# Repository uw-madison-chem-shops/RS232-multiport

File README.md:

# RS232 Multiport

## Repository

This is an open source hardware project licensed under the CERN Open Hardware Licence Version 2 - Permissive.
Please see the LICENSE file for the complete license.

## PCB

This PCB was designed using KiCAD version 7.
Refer to `mqtt_particle_sensor.pdf` for schematic.
PCB images generated with [tracespace](https://github.com/tracespace/tracespace) follow.

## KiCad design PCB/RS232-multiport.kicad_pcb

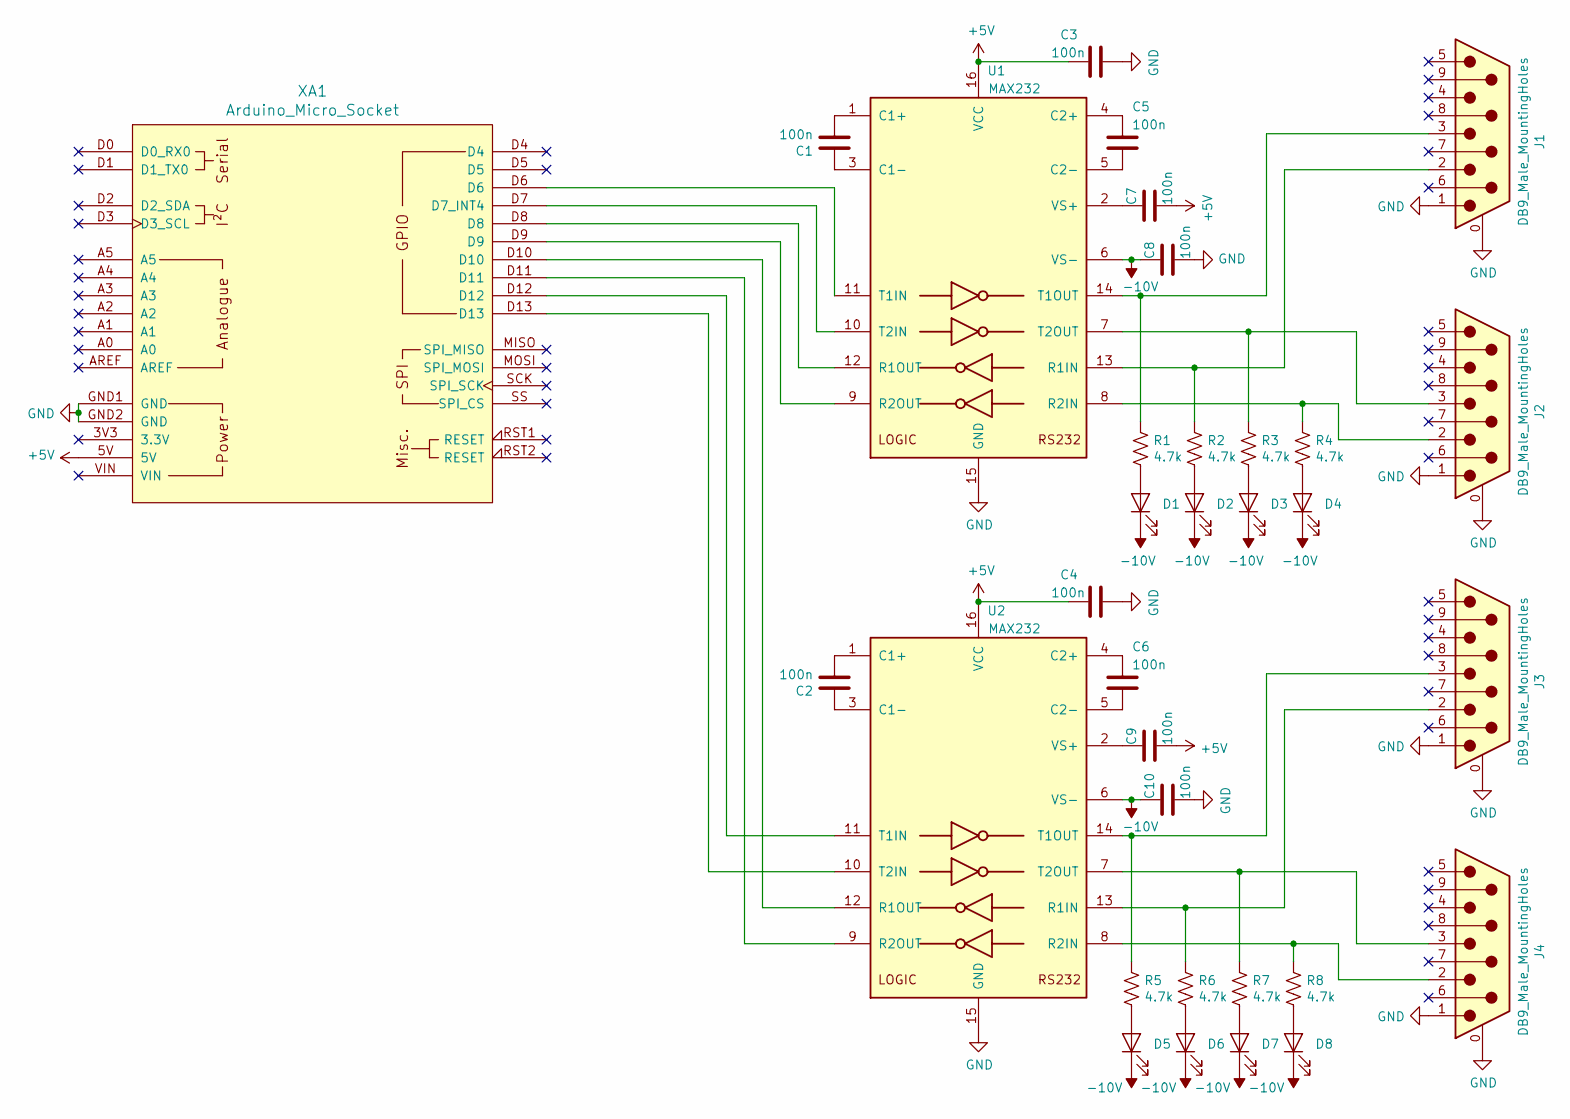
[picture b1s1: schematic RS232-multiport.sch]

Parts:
C1, C2, C3, C4, C5, C6, C7, C8, C9, C10: 100n; C_1206_3216Metric_Pad1.42x1.75mm_HandSolder
D1, D2, D3, D4, D5, D6, D7, D8: LED; LED_1206_3216Metric_Pad1.42x1.75mm_HandSolder
J1, J2, J3, J4: DB9_Male_MountingHoles; DSUB-9_Male_Horizontal_P2.77x2.84mm_EdgePinOffset9.90mm_Hou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
R1, R2, R3, R4, R5, R6, R7, R8: 4.7k; R_1206_3216Metric_Pad1.42x1.75mm_HandSolder
U1, U2: MAX232; DIP-16_W7.62mm_Socket_LongPads
XA1: Arduino_Micro_Socket

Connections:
+5V: C3.2, C4.2, C7.2, C9.2, U1.16 (VCC), U2.16 (VCC), XA1.5V
-10V: C8.1, C10.1, D1.1 (K), D2.1 (K), D3.1 (K), D4.1 (K), D5.1 (K), D6.1 (K), D7.1 (K), D8.1 (K), U1.6 (VS-), U2.6 (VS-)
GND: C3.1, C4.1, C8.2, C10.2, J1.0 (PAD), J1.1, J2.0 (PAD), J2.1, J3.0 (PAD), J3.1, J4.0 (PAD), J4.1, U1.15 (GND), U2.15 (GND), XA1.GND1 (GND), XA1.GND2 (GND)
unnamed: C1.1, U1.3 (C1-)
unnamed: C1.2, U1.1 (C1+)
unnamed: C2.1, U2.3 (C1-)
unnamed: C2.2, U2.1 (C1+)
unnamed: C5.1, U1.4 (C2+)
unnamed: C5.2, U1.5 (C2-)
unnamed: C6.1, U2.4 (C2+)
unnamed: C6.2, U2.5 (C2-)
unnamed: C7.1, U1.2 (VS+)
unnamed: C9.1, U2.2 (VS+)
unnamed: D1.2 (A), R1.2
unnamed: D2.2 (A), R2.2
unnamed: D3.2 (A), R3.2
unnamed: D4.2 (A), R4.2
unnamed: D5.2 (A), R5.2
unnamed: D6.2 (A), R6.2
unnamed: D7.2 (A), R7.2
unnamed: D8.2 (A), R8.2
unnamed: J1.2, R2.1, U1.13 (R1IN)
unnamed: J1.3, R1.1, U1.14 (T1OUT)
unnamed: J2.2, R4.1, U1.8 (R2IN)
unnamed: J2.3, R3.1, U1.7 (T2OUT)
unnamed: J3.2, R6.1, U2.13 (R1IN)
unnamed: J3.3, R5.1, U2.14 (T1OUT)
unnamed: J4.2, R8.1, U2.8 (R2IN)
unnamed: J4.3, R7.1, U2.7 (T2OUT)
unnamed: U1.9 (R2OUT), XA1.D9
unnamed: U1.10 (T2IN), XA1.D7 (D7_INT4)
unnamed: U1.11 (T1IN), XA1.D6
unnamed: U1.12 (R1OUT), XA1.D8
unnamed: U2.9 (R2OUT), XA1.D11
unnamed: U2.10 (T2IN), XA1.D13
unnamed: U2.11 (T1IN), XA1.D12
unnamed: U2.12 (R1OUT), XA1.D10

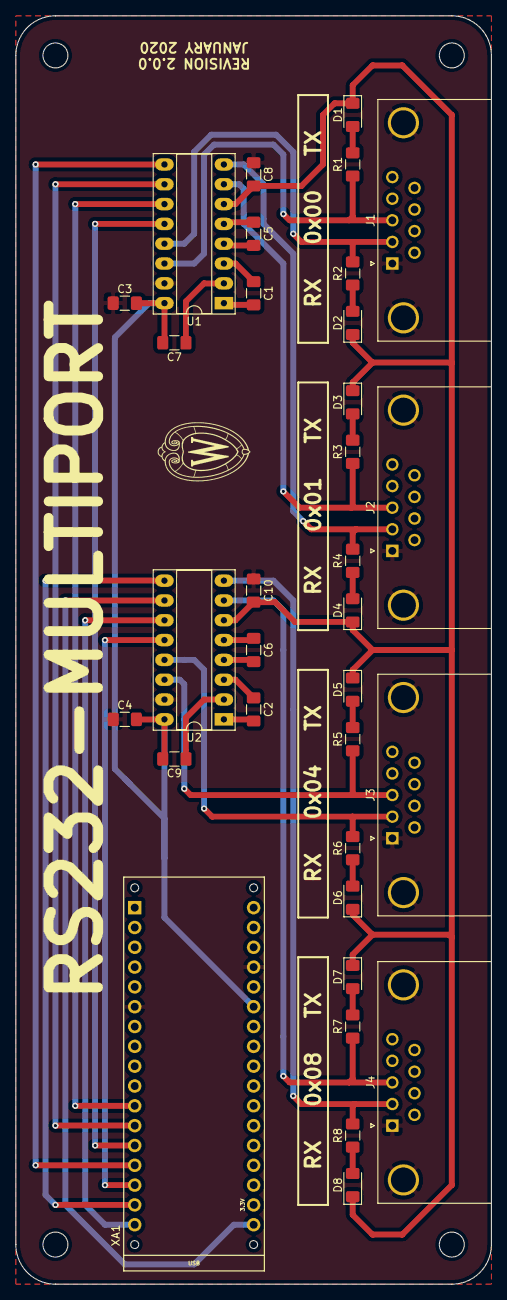
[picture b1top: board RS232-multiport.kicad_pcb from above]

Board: 2 copper layers, 61.0 x 162.6 mm, 33 parts (0 on the bottom side), 37 nets.

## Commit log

2024-06-28 tracespace
2024-06-28 license
